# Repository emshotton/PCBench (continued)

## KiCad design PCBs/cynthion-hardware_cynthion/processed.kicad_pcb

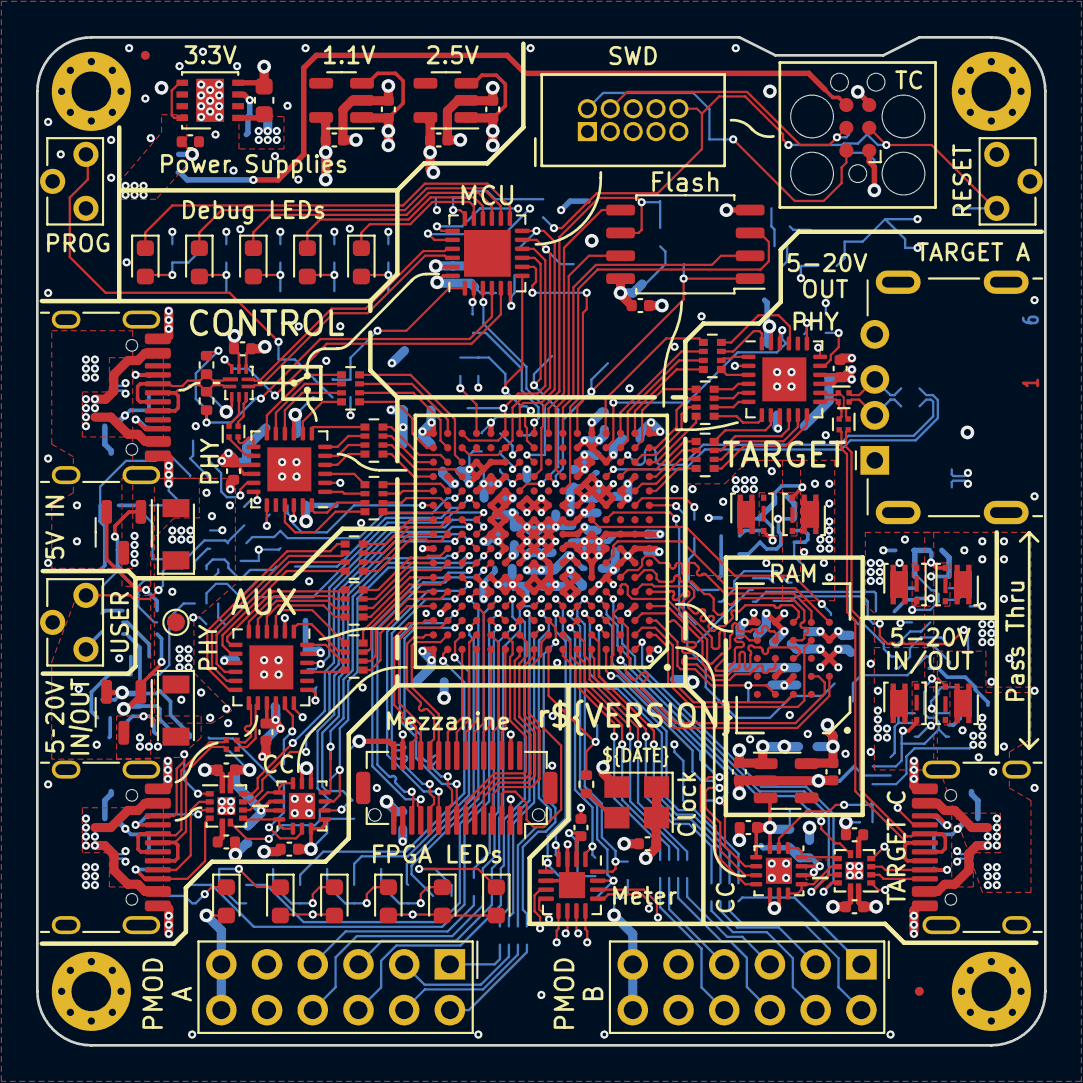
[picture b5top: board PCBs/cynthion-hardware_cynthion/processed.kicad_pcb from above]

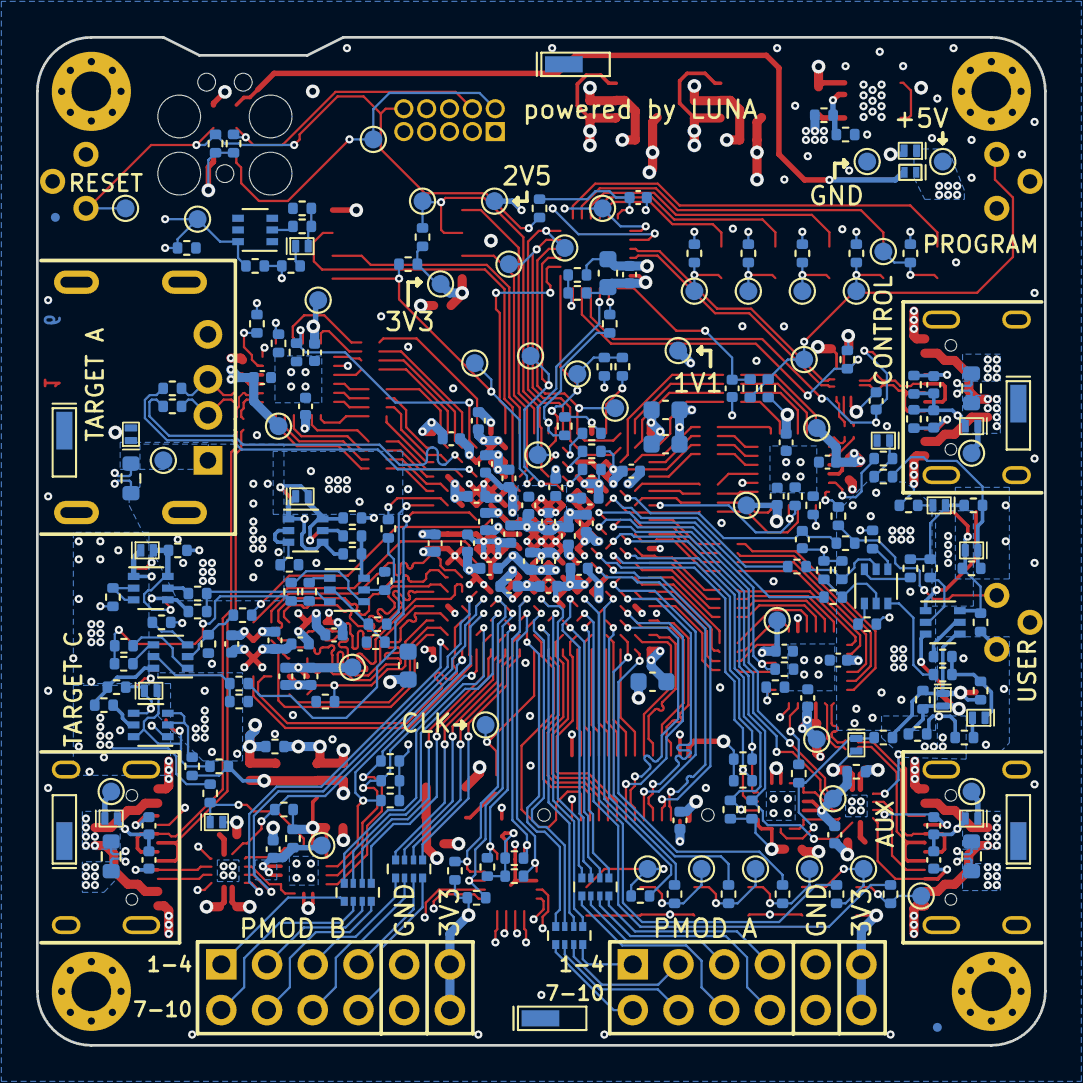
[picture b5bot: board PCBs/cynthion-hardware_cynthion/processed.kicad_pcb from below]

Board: 6 copper layers, 56.0 x 56.0 mm, 348 parts (253 on the bottom side), 337 nets.

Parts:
C1, C2, C3, C4, C20, C73: 2.2uF; C_0603_1608Metric
C5, C6, C8, C13, C16, C17, C18, C19, C21, C22, C23, C28, C29, C30, C34, C36, C37, C41, C42, C43, C48, C49, C50, C56, C58, C59, C60, C74, C76, C77, C78, C79, C80, C81, C82, C83: 1uF; C_0402_1005Metric
C7, C9, C10, C11, C12, C14, C15, C24, C26, C27, C31, C32, C33, C35, C38, C39, C40, C44, C45, C46, C51, C57, C61, C63, C64, C65, C66, C67: 0.1uF; C_0402_1005Metric
C25, C47, C52, C53, C54, C55: 330pF; C_0402_1005Metric
C62: 1nF; C_0402_1005Metric
D1, D8: D; D_SOD-123FL
D2: RED; LED_0603_1608Metric
D3: ORANGE; LED_0603_1608Metric
D4: YELLOW; LED_0603_1608Metric
D5: GREEN; LED_0603_1608Metric
D6: BLUE; LED_0603_1608Metric
D7: PURPLE; LED_0603_1608Metric
D9: SCHOTTKY; DSN1006-2
D10, D14: ICE BLUE; LED_0603_1608Metric
D11, D13: PINK; LED_0603_1608Metric
D12: WHITE; LED_0603_1608Metric
D15, D18, D22: 24±2%; DFN1006-2
D16, D19, D20, D27, D28, D29: 6.2±2%; DFN1006-2
D17, D21: 5.6±2%; DFN1006-2
D23, D24, D25, D26: TVS; DFN1006-2
D30: 3.0±2%; DFN1006-2
FID1, FID2, FID3, FID4: Fiducial; Fiducial_0.5mm_Mask1mm
FL1, FL2, FL3, FL4: Filter_EMI_CommonMode; L_CommonModeChoke_Murata_DLM0NS
H1, H2, H3, H4: MountingHole; MountingHole_2.2mm_M2_Pad_Via
IC1: ECP5-BGA256; lattice_cabga256
J1, J2, J4: USB_C; USB_C_Receptacle_HRO_TYPE-C-31-M-12
J3: USB_A; USB_A_Kycon_KUSBXHT-SB-AS1N-B30-NF_Horizontal
J5: MEZZANINE; Amphenol_10132798-03
J6: MCU_SWD; SWD_CONNECTOR_LARGE_BOX
J7: PMOD_A; PinSocket_2x06_P2.54mm_PMOD
J8: PMOD_B; PinSocket_2x06_P2.54mm_PMOD
J10: TC_SWD; Tag-Connect_TC2030-IDC-FP_2x03_P1.27mm_Vertical
J11, J12, J13, J14, J15, J16: SPRING_CONTACT; BW0033AG-L3.4W0.9H1.8
Q1, Q2, Q4, Q5, Q6, Q7: PMOS; Vishay_PowerPAK_SC70-6L_Single
Q3, Q8, Q11, Q16: 2NPN; SOT-363_SC-70-6
Q9, Q12: PMOS; SOT-23-3
Q10, Q13, Q14, Q15: 2PNP; SOT-363_SC-70-6
R1, R2, R42, R59: 0.02±1%; R_0603_1608Metric_Current_Sense
R3, R43, R47, R48, R49, R60, R61, R69, R70, R76, R77, R107: 33k; R_0402_1005Metric
R4, R16, R18, R20, R51, R53, R101, R105: 8.06k±1%; R_0402_1005Metric
R5, R8, R9, R10, R30, R31, R33, R38, R40, R63, R65, R71, R78, R83, R84, R88, R97, R98: 2.2k; R_0402_1005Metric
R6, R7, R11, R13, R34, R35, R44, R45, R46, R87, R102, R109, R110, R119: 5.1k; R_0402_1005Metric
R12, R14, R108: 330; R_0402_1005Metric
R15, R22, R23, R24, R29, R37, R39, R41, R64, R66, R72, R79, R85, R86, R89, R99, R100, R106, R111: 10k; R_0402_1005Metric
R17, R19, R21: 20k; R_0402_1005Metric
R25, R55, R56, R68, R75: 820k; R_0402_1005Metric
R26, R27, R28, R57, R58, R118: 1k; R_0402_1005Metric
R32, R36, R50, R54, R103, R112, R113, R114, R115, R116, R117: 0; R_0402_1005Metric
R52: 29.4k±1%; R_0402_1005Metric
R62, R90, R91, R92, R93, R94, R95, R96, R120: 100k; R_0402_1005Metric
R67, R73, R74, R80, R82, R104: 18.7k±1%; R_0402_1005Metric
R81: 57.6k±1%; R_0402_1005Metric
RN1, RN2, RN3, RN4: 33; R_Array_Convex_4x0402
RN5, RN6, RN7, RN8, RN9, RN10, RN11, RN12, RN13: 0; R_Array_Convex_4x0402
SW1: BTN_PROGRAM; SW_Tactile_SPST_Angled_TC-1109DE-B-F
SW2: BTN_RESET; SW_Tactile_SPST_Angled_TC-1109DE-B-F
SW3: BTN_USER; SW_Tactile_SPST_Angled_TC-1109DE-B-F
TP1, TP2, TP3, TP4, TP5, TP6, TP7, TP8, TP9, TP10, TP11, TP12, TP14, TP15, TP16, TP17, TP18, TP19, TP20, TP21, TP22, TP23, TP24, TP26, TP27, TP28, TP30, TP31, TP32, TP34, TP35, TP36, TP37, TP38, TP39, TP40, TP41, TP43, TP47, TP49, TP52, TP53, TP54, TP55: TestPoint; TestPoint_Pad_D1.0mm
U1: PAC1954; QFN-16-1EP_3x3mm_P0.5mm_EP1.45x1.45mm
U2, U12: FUSB302B; WQFN-14-1EP_2.5x2.5mm_P0.5mm_EP1.45x1.45mm
U3: 3V3REG; DFN-8-1EP_3x3mm_P0.65mm_EP1.55x2.4mm
U4: 1V15REG; SOT-23-5
U5: 2V5REG; SOT-23-5
U6: ATSAMD11; QFN-24-1EP_4x4mm_P0.5mm_EP2.6x2.6mm
U7: W25Q32JVSS; SOIC-8_5.23x5.23mm_P1.27mm
U8, U9, U11: USB3343-CP; VQFN-24-1EP_4x4mm_P0.5mm_EP2.45x2.45mm
U10: HyperRAM; BGA-24_5x5_6.0x8.0mm
U13, U14: DPO2036; Diodes_UQFN2020-12_Type-B
U15: 1V8REG; SOT-23-5
U16: PI3USB102G; Diodes_10-TQFN_ZL
Y1: Osc60MHz; Crystal_SMD_3225-4Pin_3.2x2.5mm

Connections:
+1V1: C1.1, C3.1, C7.1, C9.1, C11.1, C13.1, C15.1, C17.1, C29.1, IC1.G6 (VCC_1), IC1.G7 (VCC_2), IC1.G9 (VCC_3), IC1.L8 (VCC_4), IC1.L9 (VCC_5), IC1.L10 (VCC_6), TP4.1, U4.5 (VOUT)
+2V5: C22.1, C24.1, C26.1, C30.1, IC1.G11 (VCCAUX_1), IC1.L7 (VCCAUX_2), TP5.1, U5.5 (VOUT)
+3V3: C2.1, C4.1, C8.1, C10.1, C12.1, C14.1, C16.1, C18.1, C20.1, C23.1, C27.1, C28.1, C33.1, C34.1, C35.1, C36.1, C38.1, C39.1, C40.1, C41.1, C42.1, C44.1, C46.1, C48.1, C49.1, C56.1, C58.1, C59.1, C61.1, C66.1, C67.1, C73.1, C74.1, C79.1, C80.1, C81.1, D2.2 (A), D3.2 (A), D4.2 (A), D5.2 (A), D6.2 (A), D7.2 (A), IC1.D10 (PT47A), IC1.E6 (PT20A), IC1.E7 (PT24A), IC1.E10 (PT47B), IC1.E11 (PT51B), IC1.F6 (VCCIO0_1), IC1.F7 (VCCIO0_2), IC1.F10 (VCCIO1_1), IC1.F11 (VCCIO1_2), IC1.F12 (PR8D), IC1.H11 (VCCIO2_1), IC1.J6 (VCCIO6_1), IC1.J7 (VCCIO6_2), IC1.J11 (VCCIO2_2), IC1.J12 (PR17D), IC1.K11 (VCCIO3_1), IC1.K12 (PR29B), IC1.L4 (PL29C), IC1.L6 (VCCIO8), IC1.L11 (VCCIO3_2), IC1.L12 (PR29D), IC1.M4 (PL35C), IC1.M5 (PL44C), IC1.M6 (PL47A), IC1.M11 (PR47A), IC1.N5 (PL44D), IC1.N13 (PR38A), IC1.P4 (PL41A), IC1.P11 (PR47C), IC1.P12 (PR47D), IC1.P13 (PR41A), IC1.R5 (PL44A), IC1.R6 (D6/PB4B), J5.15, J5.16, J6.1 (VTref), J7.6, J7.12, J8.6, J8.12, J10.1, R4.1, R6.1, R7.1, R8.1, R9.1, R10.1, R11.1, R13.2, R15.1, R25.1, R32.2, R33.1, R36.2, R37.1, R38.1, R39.1, R43.1, R52.1, R54.1, R81.1, R83.1, R84.1, R85.1, R86.1, R87.1, R97.1, R98.1, R99.1, R100.1, R101.1, R106.1, R109.1, R110.1, R111.1, TP2.1, TP3.1, TP9.1, TP26.1, U1.2 (VDD), U2.3 (VDD), U2.4 (VDD), U3.1 (OUT), U4.1 (VIN), U4.3 (EN), U5.1 (VIN), U5.3 (EN), U6.24 (VDD), U7.8 (VCC), U8.2 (CLKOUT), U8.9 (VDDIO), U8.15 (VDD33), U8.16 (VBAT), U8.18 (ID), U9.2 (CLKOUT), U9.9 (VDDIO), U9.15 (VDD33), U9.16 (VBAT), U9.18 (ID), U11.2 (CLKOUT), U11.9 (VDDIO), U11.15 (VDD33), U11.16 (VBAT), U11.18 (ID), U12.3 (VDD), U12.4 (VDD), U13.12 (VSYS), U14.12 (VSYS), U15.1 (VIN), U15.3 (EN), U16.9 (VCC), Y1.1 (EN), Y1.4 (VDD)
+5V: C6.1, D1.1 (K), D8.1 (K), D9.1 (K), D19.1 (K), TP30.1, TP49.1, U3.5 (EN), U3.8 (IN)
/AUX Port/AUX PHY/CLK: RN8.8 (R1.2), U11.21 (REFCLK/XI)
/AUX Port/AUX PHY/DATA0: RN9.8 (R1.2), U11.4 (DATA0)
/AUX Port/AUX PHY/DATA1: RN9.7 (R2.2), U11.5 (DATA1)
/AUX Port/AUX PHY/DATA2: RN9.6 (R3.2), U11.6 (DATA2)
/AUX Port/AUX PHY/DATA3: RN9.5 (R4.2), U11.7 (DATA3)
/AUX Port/AUX PHY/DATA4: RN10.8 (R1.2), U11.8 (DATA4)
/AUX Port/AUX PHY/DATA5: RN10.7 (R2.2), U11.10 (DATA5)
/AUX Port/AUX PHY/DATA6: RN10.6 (R3.2), U11.11 (DATA6)
/AUX Port/AUX PHY/DATA7: RN10.5 (R4.2), U11.12 (DATA7)
/AUX Port/AUX PHY/DIR: RN8.6 (R3.2), U11.1 (DIR)
/AUX Port/AUX PHY/NXT: RN8.5 (R4.2), U11.3 (NXT)
/AUX Port/AUX PHY/PHY_D+: FL1.1, U11.14 (D+)
/AUX Port/AUX PHY/PHY_D-: FL1.3, U11.13 (D-)
/AUX Port/AUX PHY/RBIAS: R20.2, U11.19 (RBIAS)
/AUX Port/AUX PHY/STP: RN8.7 (R2.2), U11.24 (STP)
/AUX Port/AUX PHY/VBUS_CLAMPED: D15.1 (K), R21.1, R44.1, U12.2 (VBUS)
/AUX Port/AUX PHY/VBUS_SENSE: R21.2, U11.17 (VBUS)
/AUX Port/AUX PHY/VDD18: C50.1, TP35.1, U11.23 (VDD18)
/AUX Port/AUX Type C Controller/CC1: C52.1, J1.A5 (CC1), U14.3 (CC1C)
/AUX Port/AUX Type C Controller/CC1S: U12.10 (CC1), U12.11 (CC1), U14.8 (CC1S)
/AUX Port/AUX Type C Controller/CC2: C53.1, J1.B5 (CC2), U14.4 (CC2C)
/AUX Port/AUX Type C Controller/CC2S: U12.1 (CC2), U12.14 (CC2), U14.7 (CC2S)
/AUX Port/AUX Type C Controller/VCONN: C51.1, R32.1, TP37.1, U12.12 (VCONN), U12.13 (VCONN)
/AUX Port/AUX_D+: FL1.2, J1.A6 (D+), J1.B6 (D+)
/AUX Port/AUX_D-: FL1.4, J1.A7 (D-), J1.B7 (D-)
/AUX Port/AUX_PHY.CLK: IC1.D16 (PR8A), RN8.1 (R1.1)
/AUX Port/AUX_PHY.DATA0: IC1.F16 (PR14A), RN9.1 (R1.1)
/AUX Port/AUX_PHY.DATA1: IC1.G15 (PR14B), RN9.2 (R2.1)
/AUX Port/AUX_PHY.DATA2: IC1.G16 (PR20A), RN9.3 (R3.1)
/AUX Port/AUX_PHY.DATA3: IC1.H15 (PR20B), RN9.4 (R4.1)
/AUX Port/AUX_PHY.DATA4: IC1.J15 (PR23B), RN10.1 (R1.1)
/AUX Port/AUX_PHY.DATA5: IC1.J16 (PR23A), RN10.2 (R2.1)
/AUX Port/AUX_PHY.DATA6: IC1.K15 (PR23D), RN10.3 (R3.1)
/AUX Port/AUX_PHY.DATA7: IC1.K16 (PR23C), RN10.4 (R4.1)
/AUX Port/AUX_PHY.DIR: IC1.E16 (PR11D), RN8.3 (R3.1)
/AUX Port/AUX_PHY.NXT: IC1.F15 (PR11C), RN8.4 (R4.1)
/AUX Port/AUX_PHY.STP: IC1.E15 (PR8B), RN8.2 (R2.1)
/AUX Port/AUX_PHY.~RESET: IC1.J13 (PR17C), R24.1, U11.22 (~RESET)
/AUX Port/AUX_SBU1: J1.A8 (SBU1), U14.2 (SBU2C)
/AUX Port/AUX_SBU2: J1.B8 (SBU2), U14.1 (SBU1C)
/AUX Port/AUX_TYPE_C.SBU1S: IC1.H13 (PR17B), U14.9 (SBU2S)
/AUX Port/AUX_TYPE_C.SBU2S: IC1.K14 (PR20D), U14.10 (SBU1S)
/AUX Port/AUX_TYPE_C.SCL: IC1.H12 (PR17A), R38.2, U12.6 (SCL)
/AUX Port/AUX_TYPE_C.SDA: IC1.G14 (PR14C), R33.2, U12.7 (SDA)
/AUX Port/AUX_TYPE_C.~FAULT: IC1.J14 (PR20C), R99.2, U14.6 (FAULTB)
/AUX Port/AUX_TYPE_C.~INT: IC1.H14 (PR14D), R39.2, U12.5 (INT_N)
/CONTROL Port/CONTROL PHY/CLK: RN5.8 (R1.2), U8.21 (REFCLK/XI)
/CONTROL Port/CONTROL PHY/DATA0: RN6.8 (R1.2), U8.4 (DATA0)
/CONTROL Port/CONTROL PHY/DATA1: RN6.7 (R2.2), U8.5 (DATA1)
/CONTROL Port/CONTROL PHY/DATA2: RN6.6 (R3.2), U8.6 (DATA2)
/CONTROL Port/CONTROL PHY/DATA3: RN6.5 (R4.2), U8.7 (DATA3)
/CONTROL Port/CONTROL PHY/DATA4: RN7.8 (R1.2), U8.8 (DATA4)
/CONTROL Port/CONTROL PHY/DATA5: RN7.7 (R2.2), U8.10 (DATA5)
/CONTROL Port/CONTROL PHY/DATA6: RN7.6 (R3.2), U8.11 (DATA6)
/CONTROL Port/CONTROL PHY/DATA7: RN7.5 (R4.2), U8.12 (DATA7)
/CONTROL Port/CONTROL PHY/DIR: RN5.6 (R3.2), U8.1 (DIR)
/CONTROL Port/CONTROL PHY/NXT: RN5.5 (R4.2), U8.3 (NXT)
/CONTROL Port/CONTROL PHY/PHY_D+: FL3.1, U8.14 (D+)
/CONTROL Port/CONTROL PHY/PHY_D-: FL3.3, U8.13 (D-)
/CONTROL Port/CONTROL PHY/RBIAS: R16.2, U8.19 (RBIAS)
/CONTROL Port/CONTROL PHY/STP: RN5.7 (R2.2), U8.24 (STP)
/CONTROL Port/CONTROL PHY/VBUS_CLAMPED: D22.1 (K), R17.1, R46.1
/CONTROL Port/CONTROL PHY/VBUS_SENSE: R17.2, U8.17 (VBUS)
/CONTROL Port/CONTROL PHY/VDD18: C37.1, TP17.1, U8.23 (VDD18)
/CONTROL Port/CONTROL_CC1: C25.1, J2.A5 (CC1), R34.2
/CONTROL Port/CONTROL_CC2: C47.1, J2.B5 (CC2), R35.2
/CONTROL Port/CONTROL_D+: J2.A6 (D+), J2.B6 (D+), R56.2, U16.2 (D-)
/CONTROL Port/CONTROL_D-: J2.A7 (D-), J2.B7 (D-), R55.1, U16.1 (D+)
/CONTROL Port/CONTROL_MCU_D+: U6.22 (PA25), U16.6 (2D-)
/CONTROL Port/CONTROL_MCU_D-: U6.21 (PA24), U16.7 (2D+)
/CONTROL Port/CONTROL_PHY.CLK: IC1.L14 (PR32C), RN5.1 (R1.1)
/CONTROL Port/CONTROL_PHY.DATA0: IC1.N16 (PR32A), RN6.1 (R1.1)
/CONTROL Port/CONTROL_PHY.DATA1: IC1.N14 (PR35D), RN6.2 (R2.1)
/CONTROL Port/CONTROL_PHY.DATA2: IC1.P16 (PR35A), RN6.3 (R3.1)
/CONTROL Port/CONTROL_PHY.DATA3: IC1.P15 (PR32B), RN6.4 (R4.1)
/CONTROL Port/CONTROL_PHY.DATA4: IC1.R16 (PR35B), RN7.1 (R1.1)
/CONTROL Port/CONTROL_PHY.DATA5: IC1.R15 (PR38C), RN7.2 (R2.1)
/CONTROL Port/CONTROL_PHY.DATA6: IC1.T15 (PR38D), RN7.3 (R3.1)
/CONTROL Port/CONTROL_PHY.DATA7: IC1.P14 (PR38B), RN7.4 (R4.1)
/CONTROL Port/CONTROL_PHY.DIR: IC1.M16 (PR26C), RN5.3 (R3.1)
/CONTROL Port/CONTROL_PHY.NXT: IC1.M15 (PR26D), RN5.4 (R4.1)
/CONTROL Port/CONTROL_PHY.STP: IC1.L15 (PR26B), RN5.2 (R2.1)
/CONTROL Port/CONTROL_PHY.~RESET: IC1.L16 (PR26A), R22.1, U8.22 (~RESET)
/CONTROL Port/CONTROL_RESET_DETECT: C62.1, R55.2, R56.1, U6.4 (PA05)
/CONTROL Port/CONTROL_SWITCH: R15.2, U6.5 (PA06), U16.10 (S)
/Clock and Miscellaneous/CLOCK_60MHZ: IC1.A8 (PT29B), R108.1, TP1.1
/Debugger/FPGA_ADV: IC1.T6 (D7/PB4A), U6.8 (PA09/XOUT)
/Debugger/FPGA_CONFIG.DONE: IC1.P9 (DONE), TP12.1, U6.3 (PA04)
/Debugger/FPGA_CONFIG.~INIT: IC1.T9 (~INIT), R102.1, R118.1
/Debugger/FPGA_CONFIG.~PROGRAM: IC1.R9 (~PROGRAM), R5.1, R6.2, TP14.1, U6.7 (PA08/XIN)
/Debugger/FPGA_JTAG.TCK: IC1.T10 (TCK), TP21.1, U6.12 (PA15)
/Debugger/FPGA_JTAG.TDI: IC1.R11 (TDI), IC1.R14 (PR41B), TP24.1, U6.11 (PA14)
/Debugger/FPGA_JTAG.TDO: IC1.M10 (TDO), TP23.1, U6.9 (PA10)
/Debugger/FPGA_JTAG.TMS: IC1.T11 (TMS), IC1.T14 (PR41D), TP22.1, U6.10 (PA11)
/Debugger/LED10: D10.1 (K), U6.13 (PA16)
/Debugger/LED11: D11.1 (K), U6.14 (PA17)
/Debugger/LED12: D12.1 (K), U6.15 (PA22)
/Debugger/LED13: D13.1 (K), U6.16 (PA23)
/Debugger/LED14: D14.1 (K), U6.17 (PA27)
/Debugger/MCU_SWCLK: J6.4 (SWCLK/TCK), J10.4, R111.2, TP19.1, U6.19 (PA30/SWCLK)
/Debugger/MCU_SWDIO: J6.2 (SWDIO/TMS), J10.2, TP20.1, U6.20 (PA31/SWDIO)
/Debugger/~BTN_PROGRAM: C76.1, R104.1, U6.1 (PA02)
/Debugger/~BTN_RESET: J6.10 (~RESET), J10.3, R25.2, R105.1, SW2.1, TP18.1
/Expansion Interfaces/A1: J7.1, RN1.8 (R1.2)
/Expansion Interfaces/A2: J7.2, RN1.7 (R2.2)
/Expansion Interfaces/A3: J7.3, RN2.6 (R3.2)
/Expansion Interfaces/A4: J7.4, RN2.8 (R1.2)
/Expansion Interfaces/A7: J7.7, RN1.5 (R4.2)
/Expansion Interfaces/A8: J7.8, RN1.6 (R3.2)
/Expansion Interfaces/A9: J7.9, RN2.5 (R4.2)
/Expansion Interfaces/A10: J7.10, RN2.7 (R2.2)
/Expansion Interfaces/B1: J8.1, RN4.5 (R4.2)
/Expansion Interfaces/B2: J8.2, RN4.7 (R2.2)
/Expansion Interfaces/B3: J8.3, RN3.5 (R4.2)
/Expansion Interfaces/B4: J8.4, RN3.7 (R2.2)
/Expansion Interfaces/B7: J8.7, RN4.6 (R3.2)
/Expansion Interfaces/B8: J8.8, RN4.8 (R1.2)
/Expansion Interfaces/B9: J8.9, RN3.6 (R3.2)
/Expansion Interfaces/B10: J8.10, RN3.8 (R1.2)
/Expansion Interfaces/MEZZANINE3: IC1.B8 (PT35B), J5.3
/Expansion Interfaces/MEZZANINE4: IC1.A9 (PT42A), J5.4
/Expansion Interfaces/MEZZANINE5: IC1.B10 (PT44A), J5.5
/Expansion Interfaces/MEZZANINE6: IC1.A10 (PT42B), J5.6
/Expansion Interfaces/MEZZANINE7: IC1.B11 (PT49A), J5.7
/Expansion Interfaces/MEZZANINE8: IC1.D14 (PR2D), J5.8
/Expansion Interfaces/MEZZANINE9: IC1.C14 (PR2C), J5.9
/Expansion Interfaces/MEZZANINE10: IC1.F14 (PR5D), J5.10
/Expansion Interfaces/MEZZANINE11: IC1.E14 (PR5C), J5.11
/Expansion Interfaces/MEZZANINE12: IC1.G13 (PR11B), J5.12
/Expansion Interfaces/MEZZANINE13: IC1.G12 (PR11A), J5.13
/Expansion Interfaces/MEZZANINE18: IC1.C16 (PR5A), J5.18
/Expansion Interfaces/MEZZANINE19: IC1.C15 (PR5B), J5.19
/Expansion Interfaces/MEZZANINE20: IC1.B16 (PR2A), J5.20
/Expansion Interfaces/MEZZANINE21: IC1.B15 (PR2B), J5.21
/Expansion Interfaces/MEZZANINE22: IC1.A14 (PT65B), J5.22
/Expansion Interfaces/MEZZANINE23: IC1.B13 (PT60A), J5.23
/Expansion Interfaces/MEZZANINE24: IC1.A13 (PT65A), J5.24
/Expansion Interfaces/MEZZANINE25: IC1.D13 (PT62A), J5.25
/Expansion Interfaces/MEZZANINE26: IC1.A12 (PT53B), J5.26
/Expansion Interfaces/MEZZANINE27: IC1.B12 (PT56A), J5.27
/Expansion Interfaces/MEZZANINE28: IC1.A11 (PT53A), J5.28
/Expansion Interfaces/PMOD_A1: IC1.C9 (PT38B), RN1.1 (R1.1)
/Expansion Interfaces/PMOD_A2: IC1.B9 (PT38A), RN1.2 (R2.1)
/Expansion Interfaces/PMOD_A3: IC1.D11 (PT51A), RN2.3 (R3.1)
/Expansion Interfaces/PMOD_A4: IC1.C12 (PT56B), RN2.1 (R1.1)
/Expansion Interfaces/PMOD_A7: IC1.C8 (PT35A), RN1.4 (R4.1)
/Expansion Interfaces/PMOD_A8: IC1.D8 (PT33B), RN1.3 (R3.1)
/Expansion Interfaces/PMOD_A9: IC1.D9 (PT40A), RN2.4 (R4.1)
/Expansion Interfaces/PMOD_A10: IC1.C10 (PT44B), RN2.2 (R2.1)
/Expansion Interfaces/PMOD_B1: IC1.B4 (PT11B), RN4.4 (R4.1)
/Expansion Interfaces/PMOD_B2: IC1.B5 (PT15B), RN4.2 (R2.1)
/Expansion Interfaces/PMOD_B3: IC1.B6 (PT22B), RN3.4 (R4.1)
/Expansion Interfaces/PMOD_B4: IC1.B7 (PT27B), RN3.2 (R2.1)
/Expansion Interfaces/PMOD_B7: IC1.C5 (PT15A), RN4.3 (R3.1)
/Expansion Interfaces/PMOD_B8: IC1.A5 (PT18A), RN4.1 (R1.1)
/Expansion Interfaces/PMOD_B9: IC1.A6 (PT18B), RN3.3 (R3.1)
/Expansion Interfaces/PMOD_B10: IC1.A7 (PT29A), RN3.1 (R1.1)
/FPGA Bank 8 and Configuration Flash/FPGA_CFG0: IC1.N10 (CFG0), R12.1
/FPGA Bank 8 and Configuration Flash/FPGA_CFG1: IC1.P10 (CFG1), R13.1
/FPGA Bank 8 and Configuration Flash/FPGA_CFG2: IC1.R10 (CFG2), R14.1
/FPGA Bank 8 and Configuration Flash/FPGA_FLASH_CLK: IC1.N9 (MCLK/CCLK), R109.2, TP10.1, U7.6 (CLK)
/FPGA Bank 8 and Configuration Flash/IO0: IC1.T8 (D0/PICO/IO0/PB11B), U7.5 (DI(IO0))
/FPGA Bank 8 and Configuration Flash/IO1: IC1.T7 (D1/POCI/IO1/PB11A), U7.2 (DO(IO1))
/FPGA Bank 8 and Configuration Flash/IO2: IC1.M7 (D2/IO2/PB9B), U7.3 (IO2)
/FPGA Bank 8 and Configuration Flash/IO3: IC1.N7 (D3/IO3/PB9A), U7.7 (IO3)
/FPGA Bank 8 and Configuration Flash/~CS: IC1.N8 (~HOLD/DI/BUSY/~CSSPI/PB15A), R110.2, TP11.1, U7.1 (~CS)
/FPGA Bank 8 and Configuration Flash/~FPGA_SELF_PROGRAM: IC1.T13 (PR44B), R5.2
/FPGA Banks 0 and 1/LED0: IC1.E13 (PT62B), R31.2
/FPGA Banks 0 and 1/LED1: IC1.C13 (PT60B), R30.2
/FPGA Banks 0 and 1/LED2: IC1.B14 (PT67A), R29.2
/FPGA Banks 0 and 1/LED3: IC1.A15 (PT67B), R28.2
/FPGA Banks 0 and 1/LED4: IC1.D12 (PT58A), R27.2
/FPGA Banks 0 and 1/LED5: IC1.C11 (PT49B), R26.2
/FPGA Banks 0 and 1/MON.GPIO: IC1.D6 (PT20B), R86.2, U1.15 (GPIO/~ALERT2)
/FPGA Banks 0 and 1/MON.SCL: IC1.D7 (PT24B), R83.2, U1.4 (SCL)
/FPGA Banks 0 and 1/MON.SDA: IC1.C7 (PT27A), R84.2, U1.5 (SDA)
/FPGA Banks 0 and 1/MON.SLOW: IC1.C6 (PT22A), R85.2, U1.1 (SLOW/~ALERT)
/FPGA Banks 0 and 1/MON.~PWRDN: IC1.D5 (PT13B), R87.2, U1.16 (~PWRDN)
/FPGA Banks 0 and 1/TARGET_C.SBU1S: IC1.A2 (PT4A), U13.10 (SBU1S)
/FPGA Banks 0 and 1/TARGET_C.SBU2S: IC1.E4 (PT9A), U13.9 (SBU2S)
/FPGA Banks 0 and 1/TARGET_C.SCL: IC1.A4 (PT6B), R98.2, U2.6 (SCL)
/FPGA Banks 0 and 1/TARGET_C.SDA: IC1.C4 (PT11A), R97.2, U2.7 (SDA)
/FPGA Banks 0 and 1/TARGET_C.~FAULT: IC1.D4 (PT9B), R100.2, U13.6 (FAULTB)
/FPGA Banks 0 and 1/TARGET_C.~INT: IC1.A3 (PT6A), R37.2, U2.5 (INT_N)
/FPGA Banks 2 and 3/~AUX_VBUS_IN_EN: IC1.L13 (PR29C), R78.2
/FPGA Banks 2 and 3/~BTN_USER: C78.1, IC1.M14 (PR32D), R107.1
/FPGA Banks 2 and 3/~CONTROL_VBUS_IN_EN: IC1.K13 (PR29A), R71.2
/FPGA Banks 6 and 7/AUX_VBUS_EN: IC1.L2 (PL26B), R63.2
/FPGA Banks 6 and 7/CONTROL_VBUS_EN: IC1.L1 (PL26A), R40.2
/FPGA Banks 6 and 7/RAM.CK: IC1.C3 (PL2C), U10.B2 (CK)
/FPGA Banks 6 and 7/RAM.DQ0: IC1.F2 (PL11C), U10.D3 (DQ0)
/FPGA Banks 6 and 7/RAM.DQ1: IC1.B1 (PL2A), U10.D2 (DQ1)
/FPGA Banks 6 and 7/RAM.DQ2: IC1.C2 (PL5B), U10.C4 (DQ2)
/FPGA Banks 6 and 7/RAM.DQ3: IC1.E1 (PL11D), U10.D4 (DQ3)
/FPGA Banks 6 and 7/RAM.DQ4: IC1.E3 (PL5C), U10.D5 (DQ4)
/FPGA Banks 6 and 7/RAM.DQ5: IC1.E2 (PL8B), U10.E3 (DQ5)
/FPGA Banks 6 and 7/RAM.DQ6: IC1.F3 (PL5D), U10.E2 (DQ6)
/FPGA Banks 6 and 7/RAM.DQ7: IC1.G4 (PL11B), U10.E1 (DQ7)
/FPGA Banks 6 and 7/RAM.RWDS: IC1.D1 (PL8A), U10.C3 (RWDS)
/FPGA Banks 6 and 7/RAM.~CK: IC1.D3 (PL2D), U10.B1 (~CK)
/FPGA Banks 6 and 7/RAM.~CS: IC1.B2 (PL2B), U10.A3 (~CS)
/FPGA Banks 6 and 7/RAM.~RESET: IC1.C1 (PL5A), R119.1, U10.A4 (~RESET)
/FPGA Banks 6 and 7/TARGET_A_DISCHARGE: IC1.K4 (PL29A), R88.2
/FPGA Banks 6 and 7/TARGET_C_VBUS_EN: IC1.K5 (PL29B), R65.2
/FPGA Banks 6 and 7/TARGET_FS_MONITOR_D+: IC1.N4 (PL38A), R58.2
/FPGA Banks 6 and 7/TARGET_FS_MONITOR_D-: IC1.P3 (PL38B), R57.2
/FPGA Banks 6 and 7/TARGET_PHY.CLK: IC1.T4 (PL44B), RN11.1 (R1.1)
/FPGA Banks 6 and 7/TARGET_PHY.DATA0: IC1.R2 (PL38C), RN12.1 (R1.1)
/FPGA Banks 6 and 7/TARGET_PHY.DATA1: IC1.R1 (PL35B), RN12.2 (R2.1)
/FPGA Banks 6 and 7/TARGET_PHY.DATA2: IC1.P2 (PL32B), RN12.3 (R3.1)
/FPGA Banks 6 and 7/TARGET_PHY.DATA3: IC1.P1 (PL35A), RN12.4 (R4.1)
/FPGA Banks 6 and 7/TARGET_PHY.DATA4: IC1.N3 (PL35D), RN13.1 (R1.1)
/FPGA Banks 6 and 7/TARGET_PHY.DATA5: IC1.N1 (PL32A), RN13.2 (R2.1)
/FPGA Banks 6 and 7/TARGET_PHY.DATA6: IC1.M2 (PL26D), RN13.3 (R3.1)
/FPGA Banks 6 and 7/TARGET_PHY.DATA7: IC1.M1 (PL26C), RN13.4 (R4.1)
/FPGA Banks 6 and 7/TARGET_PHY.DIR: IC1.R3 (PL41B), RN11.3 (R3.1)
/FPGA Banks 6 and 7/TARGET_PHY.NXT: IC1.T2 (PL38D), RN11.4 (R4.1)
/FPGA Banks 6 and 7/TARGET_PHY.STP: IC1.T3 (PL41D), RN11.2 (R2.1)
/FPGA Banks 6 and 7/TARGET_PHY.~RESET: IC1.R4 (PL41C), R23.1, U9.22 (~RESET)
/Power Distribution and Monitoring/~POWER_GOOD: Q16.6 (C1), R43.2, R103.2, R112.2, R113.2, R114.2, R115.2, R116.2, R117.2, TP8.1
/TARGET Port/TARGET PHY/CLK: RN11.8 (R1.2), U9.21 (REFCLK/XI)
/TARGET Port/TARGET PHY/DATA0: RN12.8 (R1.2), U9.4 (DATA0)
/TARGET Port/TARGET PHY/DATA1: RN12.7 (R2.2), U9.5 (DATA1)
/TARGET Port/TARGET PHY/DATA2: RN12.6 (R3.2), U9.6 (DATA2)
/TARGET Port/TARGET PHY/DATA3: RN12.5 (R4.2), U9.7 (DATA3)
/TARGET Port/TARGET PHY/DATA4: RN13.8 (R1.2), U9.8 (DATA4)
/TARGET Port/TARGET PHY/DATA5: RN13.7 (R2.2), U9.10 (DATA5)
/TARGET Port/TARGET PHY/DATA6: RN13.6 (R3.2), U9.11 (DATA6)
/TARGET Port/TARGET PHY/DATA7: RN13.5 (R4.2), U9.12 (DATA7)
/TARGET Port/TARGET PHY/DIR: RN11.6 (R3.2), U9.1 (DIR)
/TARGET Port/TARGET PHY/NXT: RN11.5 (R4.2), U9.3 (NXT)
/TARGET Port/TARGET PHY/PHY_D+: FL2.1, FL4.1, U9.14 (D+)
/TARGET Port/TARGET PHY/PHY_D-: FL2.3, FL4.3, U9.13 (D-)
/TARGET Port/TARGET PHY/RBIAS: R18.2, U9.19 (RBIAS)
/TARGET Port/TARGET PHY/STP: RN11.7 (R2.2), U9.24 (STP)
/TARGET Port/TARGET PHY/VBUS_CLAMPED: D18.1 (K), R19.1, R45.1, U2.2 (VBUS)
/TARGET Port/TARGET PHY/VBUS_SENSE: R19.2, U9.17 (VBUS)
/TARGET Port/TARGET PHY/VDD18: C43.1, TP27.1, U9.23 (VDD18)
/TARGET Port/TARGET Type C Controller/CC1: C54.1, J4.A5 (CC1), U13.3 (CC1C)
/TARGET Port/TARGET Type C Controller/CC1S: U2.10 (CC1), U2.11 (CC1), U13.8 (CC1S)
/TARGET Port/TARGET Type C Controller/CC2: C55.1, J4.B5 (CC2), U13.4 (CC2C)
/TARGET Port/TARGET Type C Controller/CC2S: U2.1 (CC2), U2.14 (CC2), U13.7 (CC2S)
/TARGET Port/TARGET Type C Controller/SBU1: J4.A8 (SBU1), U13.1 (SBU1C)
/TARGET Port/TARGET Type C Controller/SBU2: J4.B8 (SBU2), U13.2 (SBU2C)
/TARGET Port/TARGET Type C Controller/VCONN: C45.1, R36.1, TP36.1, U2.12 (VCONN), U2.13 (VCONN)
/TARGET Port/TARGET_A_D+: FL2.2, J3.3 (D+), R58.1
/TARGET Port/TARGET_A_D-: FL2.4, J3.2 (D-), R57.1
/TARGET Port/TARGET_C_D+: FL4.2, J4.A6 (D+), J4.B6 (D+)
/TARGET Port/TARGET_C_D-: FL4.4, J4.A7 (D-), J4.B7 (D-)
AUX_SENSE+: R42.3, U1.8 (SENSE3+)
AUX_SENSE-: R42.2, U1.7 (SENSE3-)
AUX_VBUS: D25.1 (K), J1.A4 (VBUS), J1.A9 (VBUS), J1.B4 (VBUS), J1.B9 (VBUS), R42.4, TP34.1
AUX_VBUS_IN: D20.1 (K), Q4.1 (D), Q10.4 (E2), Q12.2 (S), R42.1, R44.2, R74.1, R75.1
CONTROL_SENSE+: R1.2, U1.10 (SENSE4+)
CONTROL_SENSE-: R1.3, U1.9 (SENSE4-)
CONTROL_VBUS: D23.1 (K), J2.A4 (VBUS), J2.A9 (VBUS), J2.B4 (VBUS), J2.B9 (VBUS), R1.1, TP16.1
CONTROL_VBUS_IN: D16.1 (K), Q1.1 (D), Q9.2 (S), Q10.1 (E1), R1.4, R46.2, R67.1, R68.1
GND: C1.2, C2.2, C3.2, C4.2, C5.2, C6.2, C7.2, C8.2, C9.2, C10.2, C11.2, C12.2, C13.2, C14.2, C15.2, C16.2, C17.2, C18.2, C19.2, C20.2, C21.2, C22.2, C23.2, C24.2, C25.2, C26.2, C27.2, C28.2, C29.2, C30.2, C31.2, C32.2, C33.2, C34.2, C35.2, C36.2, C37.2, C38.2, C39.2, C40.2, C41.2, C42.2, C43.2, C44.2, C45.2, C46.2, C47.2, C48.2, C49.2, C50.2, C51.2, C52.2, C53.2, C54.2, C55.2, C56.2, C57.2, C58.2, C59.2, C60.2, C61.2, C62.2, C63.2, C64.2, C65.2, C66.2, C67.2, C73.2, C74.2, C76.2, C77.2, C78.2, C79.2, C80.2, C81.2, C82.2, C83.2, D15.2 (A), D18.2 (A), D19.2 (A), D22.2 (A), D23.2 (A), D24.2 (A), D25.2 (A), D26.2 (A), H1.1, H2.1, H3.1, H4.1, IC1.A1 (GND_1), IC1.A16 (GND_2), IC1.D2 (GND_3), IC1.D15 (GND_4), IC1.E5 (PT13A), IC1.E8 (PT33A), IC1.E9 (PT40B), IC1.E12 (PT58B), IC1.F4 (PL8C), IC1.F8 (GND_5), IC1.F9 (GND_6), IC1.F13 (PR8C), IC1.G2 (PL14B), IC1.G3 (PL14C), IC1.G8 (GND_7), IC1.G10 (GND_8), IC1.H1 (GND_9), IC1.H2 (PL20B), IC1.H3 (PL14D), IC1.H8 (GND_10), IC1.H9 (GND_11), IC1.H10 (GND_12), IC1.H16 (GND_13), IC1.J8 (GND_14), IC1.J9 (GND_15), IC1.J10 (GND_16), IC1.K6 (GND_17), IC1.K7 (GND_18), IC1.K8 (GND_19), IC1.K9 (GND_20), IC1.K10 (GND_21), IC1.L3 (PL32C), IC1.L5 (PL29D), IC1.M3 (PL32D), IC1.M12 (PR44C), IC1.M13 (PR35C), IC1.N2 (GND_22), IC1.N6 (PL47B), IC1.N11 (PR47B), IC1.N12 (PR44D), IC1.N15 (GND_23), IC1.P5 (PL47D), IC1.P6 (PL47C), IC1.T1 (GND_24), IC1.T5 (GND_25), IC1.T12 (GND_26), IC1.T16 (GND_27), J1.A1 (GND), J1.A12 (GND), J1.B1 (GND), J1.B12 (GND), J1.S1 (SHIELD), J2.A1 (GND), J2.A12 (GND), J2.B1 (GND), J2.B12 (GND), J2.S1 (SHIELD), J3.4 (GND), J3.5 (Shield), J4.A1 (GND), J4.A12 (GND), J4.B1 (GND), J4.B12 (GND), J4.S1 (SHIELD), J5.2, J5.14, J5.17, J5.29, J5.MP (MountPin), J6.3 (GND), J6.5 (GND), J6.9 (GNDDetect), J7.5, J7.11, J8.5, J8.11, J10.5, J11.1, J12.1, J13.1, J14.1, J15.1, J16.1, Q16.1 (E1), R12.2, R14.2, R16.1, R18.1, R20.1, R22.2, R23.2, R24.2, R34.1, R35.1, R41.2, R51.2, R53.2, R64.2, R66.2, R70.2, R72.2, R73.2, R77.2, R79.2, R80.2, R82.2, R89.2, R90.1, R91.1, R94.1, R95.1, R96.1, R102.2, R117.1, R119.2, R120.1, SW1.2, SW1.3 (SHIELD), SW2.2, SW2.3 (SHIELD), SW3.2, SW3.3 (SHIELD), TP28.1, U1.3 (GND), U1.6 (ADDRSEL), U1.17 (GND), U2.8 (GND), U2.9 (GND), U2.15 (GND), U3.4 (GND), U3.9 (GND), U4.2 (GND), U5.2 (GND), U6.23 (GND), U7.4 (GND), U8.25 (GND), U9.25 (GND), U10.B3 (VSS), U10.C1 (VSSQ), U10.E5 (VSSQ), U11.25 (GND), U12.8 (GND), U12.9 (GND), U12.15 (GND), U13.11 (GND), U13.13 (GND), U14.11 (GND), U14.13 (GND), U15.2 (GND), U16.3 (GND), U16.8 (~OE), Y1.2 (GND)
unnamed: D1.2 (A), Q12.3 (D)
unnamed: D2.1 (K), R26.1, TP43.1
unnamed: D3.1 (K), R27.1, TP47.1
unnamed: D4.1 (K), R28.1, TP52.1
unnamed: D5.1 (K), R29.1, TP53.1
unnamed: D6.1 (K), R30.1, TP54.1
unnamed: D7.1 (K), R31.1, TP55.1
unnamed: D8.2 (A), Q9.3 (D)
unnamed: D9.2 (A), J10.6
unnamed: D10.2 (A), R7.2, TP31.1
unnamed: D11.2 (A), R8.2, TP32.1
unnamed: D12.2 (A), R9.2, TP38.1
unnamed: D13.2 (A), R10.2, TP39.1
unnamed: D14.2 (A), R11.2, TP41.1
unnamed: D16.2 (A), Q9.1 (G), Q10.6 (C1), R68.2, R70.1
unnamed: D17.2 (A), R73.1
unnamed: D17.1 (K), R47.2, R67.2, R69.1
unnamed: D20.2 (A), Q10.3 (C2), Q12.1 (G), R75.2, R77.1
unnamed: D21.2 (A), R80.1
unnamed: D21.1 (K), R48.2, R74.2, R76.1
unnamed: D27.2 (A), Q1.3 (G), Q2.3 (G), Q13.6 (C1), R90.2
unnamed: D27.1 (K), Q1.4 (S), Q2.4 (S), Q13.1 (E1), Q13.4 (E2), R3.1
unnamed: D28.2 (A), Q4.3 (G), Q5.3 (G), Q14.6 (C1), R94.2
unnamed: D28.1 (K), Q4.4 (S), Q5.4 (S), Q14.1 (E1), Q14.4 (E2), R60.1
unnamed: D29.2 (A), Q6.3 (G), Q7.3 (G), Q15.6 (C1), R96.2
unnamed: D29.1 (K), Q6.4 (S), Q7.4 (S), Q15.1 (E1), Q15.4 (E2), R61.1
unnamed: D30.2 (A), R50.1, R51.1
unnamed: D30.1 (K), R4.2
unnamed: Q3.2 (B1), R40.1, R41.1
unnamed: Q3.6 (C1), R3.2, R62.1
unnamed: Q3.1 (E1), R112.1
unnamed: Q3.5 (B2), R63.1, R64.1
unnamed: Q3.3 (C2), R60.2, R92.1
unnamed: Q3.4 (E2), R115.1
unnamed: Q8.2 (B1), R65.1, R66.1
unnamed: Q8.6 (C1), R61.2, R93.1
unnamed: Q8.1 (E1), R114.1
unnamed: Q8.5 (B2), R88.1, R89.1
unnamed: Q8.3 (C2), R49.2
unnamed: Q8.4 (E2), R103.1
unnamed: Q10.2 (B1), R47.1
unnamed: Q10.5 (B2), R48.1
unnamed: Q11.2 (B1), R71.1, R72.1
unnamed: Q11.6 (C1), R69.2
unnamed: Q11.1 (E1), R113.1
unnamed: Q11.5 (B2), R78.1, R79.1
unnamed: Q11.3 (C2), R76.2
unnamed: Q11.4 (E2), R116.1
unnamed: Q13.2 (B1), Q13.3 (C2), R91.2
unnamed: Q13.5 (B2), R62.2
unnamed: Q14.2 (B1), Q14.3 (C2), R95.2
unnamed: Q14.5 (B2), R92.2
unnamed: Q15.2 (B1), Q15.3 (C2), R120.2
unnamed: Q15.5 (B2), R93.2
unnamed: Q16.2 (B1), R50.2
unnamed: R101.2, R104.2, SW1.1, TP15.1
unnamed: R106.2, R107.2, SW3.1
unnamed: R81.2, R82.1, U3.3 (ADJ/NC)
unnamed: R118.2, U6.2 (PA03)
unnamed: R52.2, R53.1, U6.6 (PA07)
unnamed: C77.1, R105.2, U6.18 (PA28/~RST)
unnamed: C57.1, U13.5 (CB)
unnamed: C63.1, U14.5 (CB)
unnamed: FL3.4, U16.5 (1D+)
unnamed: FL3.2, U16.4 (1D-)
unnamed: R108.2, Y1.3 (OUT)
TARGET_A_SENSE+: R2.3, U1.11 (SENSE1+)
TARGET_A_SENSE-: R2.2, U1.12 (SENSE1-)
TARGET_A_VBUS: D24.1 (K), J3.1 (VBUS), R2.4, TP7.1
TARGET_A_VBUS_IN: Q2.1 (D), Q5.1 (D), Q6.1 (D), R2.1, R49.1
TARGET_C_SENSE+: R59.3, U1.13 (SENSE2+)
TARGET_C_SENSE-: R59.2, U1.14 (SENSE2-)
TARGET_C_VBUS: D26.1 (K), J4.A4 (VBUS), J4.A9 (VBUS), J4.B4 (VBUS), J4.B9 (VBUS), R59.4, TP40.1
TARGET_C_VBUS_IN: Q7.1 (D), R45.2, R59.1
VCCRAM: C5.1, C19.1, C21.1, C31.1, C32.1, C60.1, C64.1, C65.1, C82.1, C83.1, IC1.F5 (PL8D), IC1.G5 (PL11A), IC1.H4 (PL17B), IC1.H5 (PL17A), IC1.H6 (VCCIO7_1), IC1.H7 (VCCIO7_2), IC1.J1 (PL23A), IC1.J2 (PL23B), IC1.J3 (PL20C), IC1.J4 (PL17C), IC1.J5 (PL17D), R54.2, TP6.1, U10.B4 (VCC), U10.D1 (VCCQ), U10.E4 (VCCQ), U15.5 (VOUT)

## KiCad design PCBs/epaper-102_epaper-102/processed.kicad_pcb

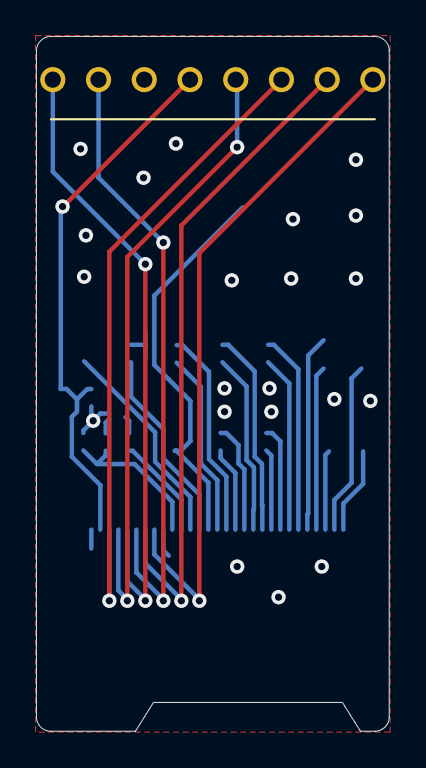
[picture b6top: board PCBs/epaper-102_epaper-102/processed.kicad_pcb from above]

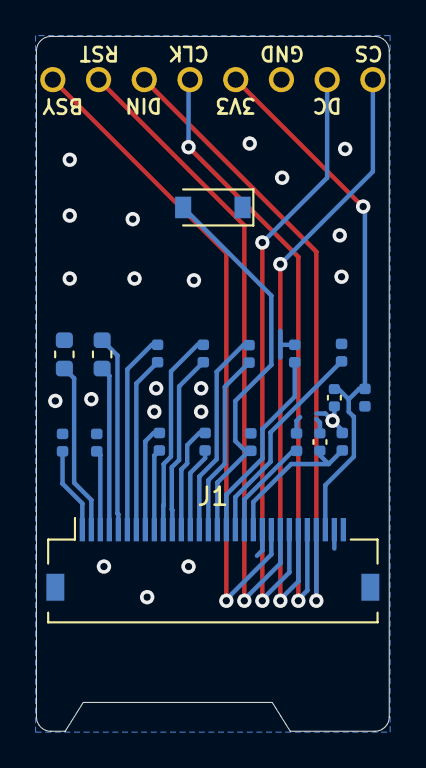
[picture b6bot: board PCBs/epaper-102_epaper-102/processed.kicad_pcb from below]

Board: 2 copper layers, 19.6 x 38.6 mm, 20 parts (20 on the bottom side), 28 nets.

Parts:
C1: 4.7uF; C_0402_1005Metric
C2, C3, C4, C5, C6, C7, C8, C9, C10, C11, C13, C15: 1uF; C_0402_1005Metric
C12, C14: 2.2uF; C_0603_1608Metric
C16, C17: .1uF; C_0402_1005Metric
D1: D; D_SOD-123
J1: Conn_01x30_Female; Hirose_FH12-30S-0.5SH_1x30-1MP_P0.50mm_Horizontal
J2: Conn_01x08_Female; PinHeader_1x08_P2.54mm_Vertical

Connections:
3V3: C1.1, C16.1, J1.28, J2.4
BUSY: J1.22, J2.8
CLK: J1.26, J2.5
CS: J1.25, J2.1
DC: J1.24, J2.2
DIN: J1.27, J2.6
GND: C1.2, C2.1, C3.1, C4.1, C5.1, C7.1, C13.1, C14.1, C15.1, C16.2, C17.1, D1.1, J1.21, J1.29, J2.3
unnamed: C3.2, J1.19
unnamed: C4.2, J1.18
unnamed: C5.2, J1.17
unnamed: C6.1, J1.14
unnamed: C6.2, J1.15
unnamed: C7.2, D1.2, J1.16
unnamed: C8.1, J1.12
unnamed: C8.2, J1.13
unnamed: C9.1, J1.10
unnamed: C9.2, J1.11
unnamed: C10.1, J1.8
unnamed: C10.2, J1.9
unnamed: C11.1, J1.6
unnamed: C11.2, J1.7
unnamed: C12.1, J1.4
unnamed: C12.2, J1.5
unnamed: C13.2, J1.3
unnamed: C14.2, J1.2
unnamed: C15.2, J1.1
unnamed: C2.2, C17.2, J1.20
RST: J1.23, J2.7

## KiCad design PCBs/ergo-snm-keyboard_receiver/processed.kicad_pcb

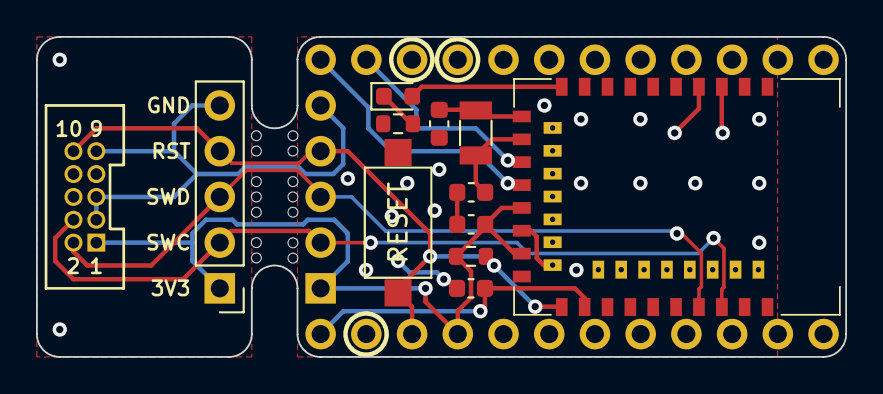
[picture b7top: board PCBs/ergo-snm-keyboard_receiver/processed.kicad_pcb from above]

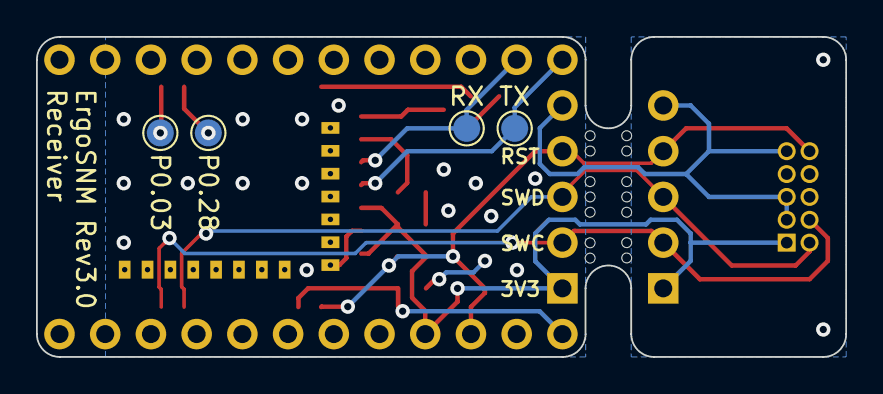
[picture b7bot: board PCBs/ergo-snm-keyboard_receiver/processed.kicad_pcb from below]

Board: 2 copper layers, 45.0 x 17.8 mm, 33 parts (6 on the bottom side), 14 nets.

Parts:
C1, C2: 12pF; C_0603_1608Metric
C3, C4: 10uF; C_0603_1608Metric
H1, H2, H3, H4, H5, H6, H7, H8, H9, H10, H11, H12, H13, H14: MountingHole; Mouse bite
J1: Conn_02x05_Counter_Clockwise; PinHeader_2x05_P1.27mm_Vertical
J2, J4: Conn_01x13; PinHeader_1x12_P2.54mm_Vertical
J3, J5: Conn_01x04; PinHeader_1x05_P2.54mm_Vertical
LD1: Red; LED_0603_1608Metric
R1: 10k; R_0603_1608Metric
R2: 1k; R_0603_1608Metric
SW1: RESET; SW_SPST_CK_RS282G05A3
TP1, TP2, TP3, TP4: TestPoint; TestPoint_Pad_D1.5mm
U1: E73-2G4M08S1C; E73-2G4M08S1C-52840
Y1: 32.768kHz; Crystal_SMD_3215-2Pin_3.2x1.5mm

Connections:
+3.3V: C3.1, J1.1, J3.1, J4.4, J5.1, R1.1, U1.19 (VDD), U1.23 (VDDH)
+5V: C4.1, J4.1, U1.27 (VBUS)
GND: C1.2, C2.1, C3.2, C4.2, J1.3, J1.5, J1.9, J2.3, J2.4, J3.5, J4.2, J5.5, R2.2, SW1.1, U1.5 (GND), U1.21 (GND), U1.24 (GND)
LED: LD1.2 (A), U1.10 (P0.30)
unnamed: LD1.1 (K), R2.1
unnamed: C1.1, U1.11 (P0.00/XL1), Y1.2
unnamed: C2.2, U1.13 (P0.01/XL2), Y1.1
unnamed: TP1.1, U1.3 (P0.03)
unnamed: TP2.1, U1.4 (P0.28)
RX: J2.2, TP4.1, U1.15 (P0.05)
SWC: J1.4, J3.2, J5.2, U1.39 (SWCLK)
SWD: J1.2, J3.3, J5.3, U1.37 (SWDIO)
TX: J2.1, TP3.1, U1.17 (P1.09)
~RESET: J1.10, J3.4, J4.3, J5.4, R1.2, SW1.2, U1.26 (P0.18/RST)
